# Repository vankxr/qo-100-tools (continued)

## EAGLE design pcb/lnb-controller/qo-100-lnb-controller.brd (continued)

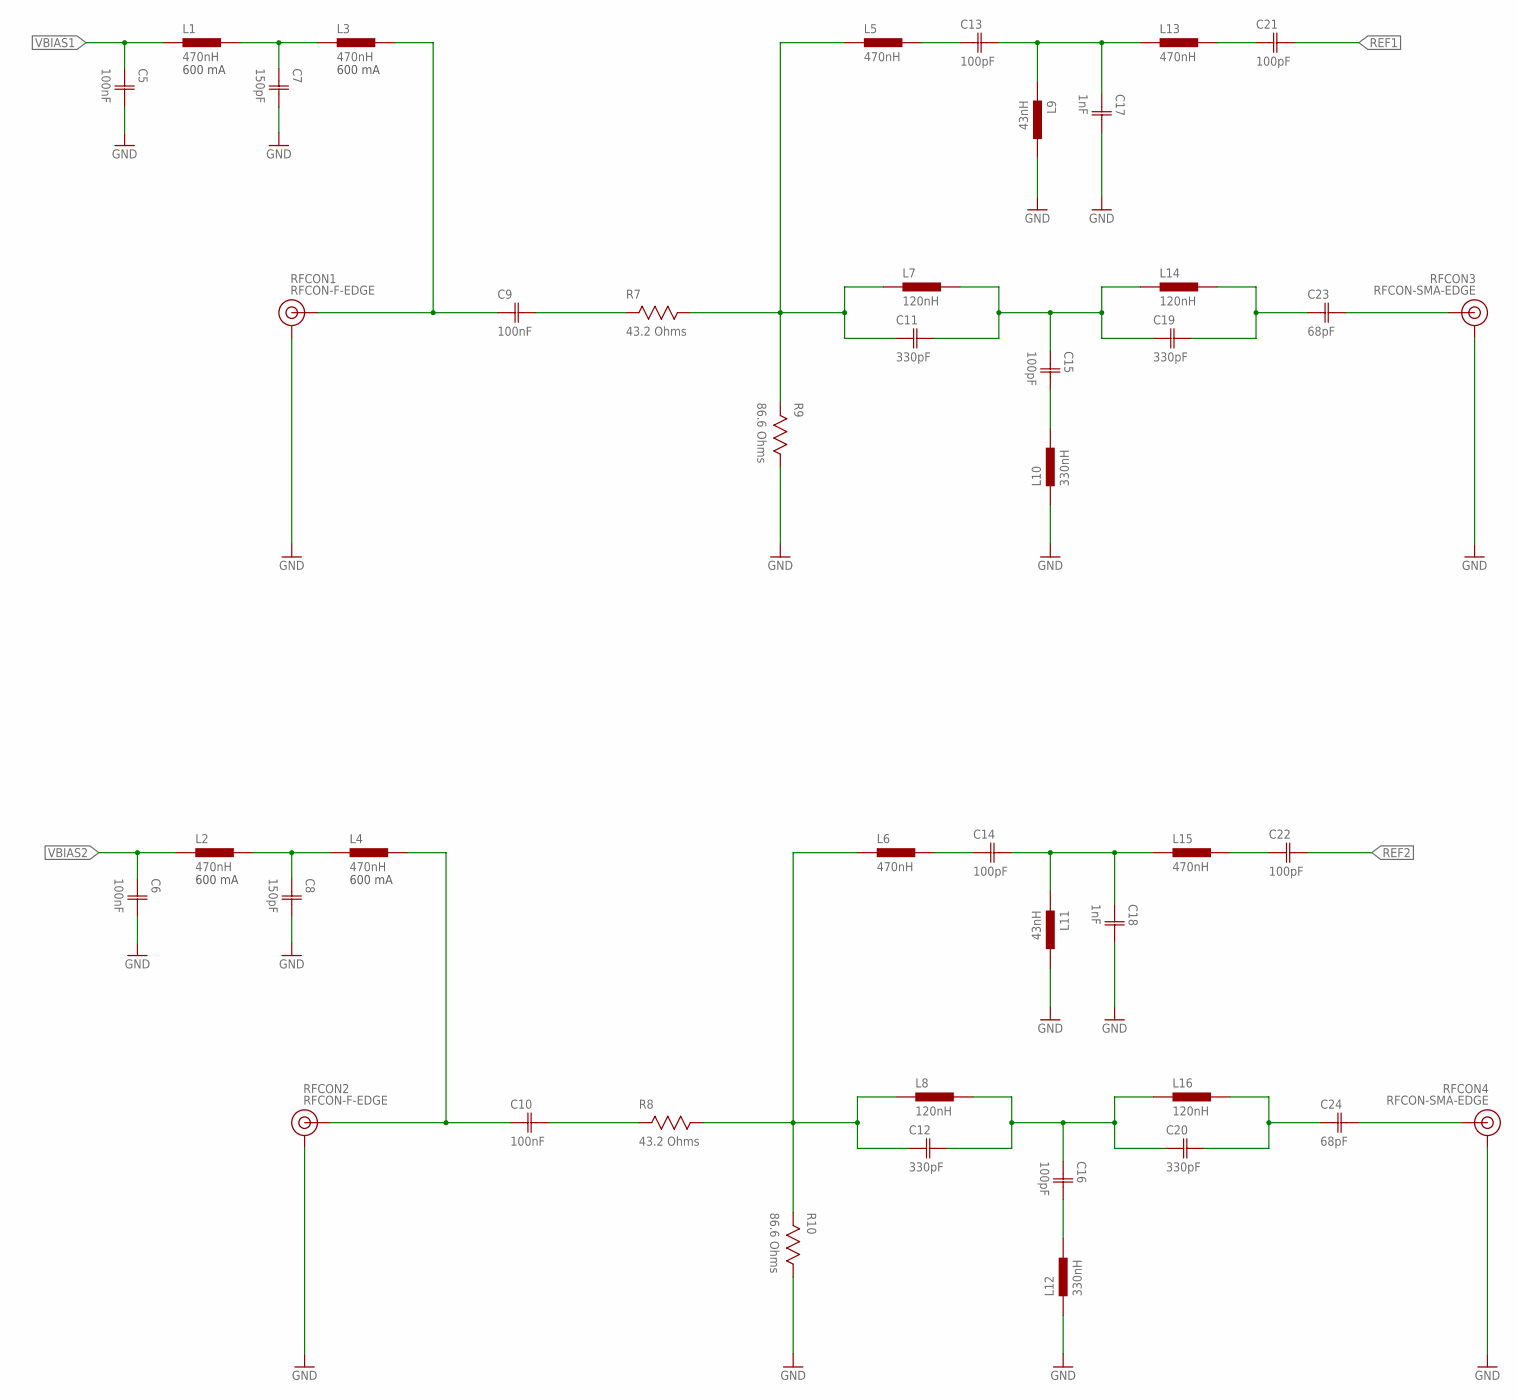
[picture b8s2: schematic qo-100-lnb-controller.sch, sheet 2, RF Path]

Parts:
C5, C6, C9, C10: 100nF; CAP0603
C7, C8: 150pF; CAP0603
C11, C12, C19, C20: 330pF; CAP0603
C13, C14, C15, C16, C21, C22: 100pF; CAP0603
C17, C18: 1nF; CAP0603
C23, C24: 68pF; CAP0603
L1, L2, L3, L4, L5, L6, L13, L15: 470nH; IND0603
L7, L8, L14, L16: 120nH; IND0603
L9, L11: 43nH; IND0603
L10, L12: 330nH; IND0603
R7, R8: 43.2 Ohms; RES0603
R9, R10: 86.6 Ohms; RES0603
RFCON1, RFCON2: RFCON-F-EDGE; F-EDGE
RFCON3, RFCON4: RFCON-SMA-EDGE; SMA-EDGE

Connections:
GND: C5.2 (C2), C6.2 (C2), C7.2 (C2), C8.2 (C2), C17.2 (C2), C18.2 (C2), L9.2, L10.1, L11.2, L12.1, R9.1, R10.1, RFCON1.GND@0 (GND), RFCON1.GND@1 (GND), RFCON1.GND@2 (GND), RFCON1.GND@3 (GND), RFCON1.GND@4 (GND), RFCON1.GND@5 (GND), RFCON2.GND@0 (GND), RFCON2.GND@1 (GND), RFCON2.GND@2 (GND), RFCON2.GND@3 (GND), RFCON2.GND@4 (GND), RFCON2.GND@5 (GND), RFCON3.GND@0 (GND), RFCON3.GND@1 (GND), RFCON3.GND@2 (GND), RFCON3.GND@3 (GND), RFCON4.GND@0 (GND), RFCON4.GND@1 (GND), RFCON4.GND@2 (GND), RFCON4.GND@3 (GND); also elsewhere on the board
unnamed: C9.1 (C1), L3.2, RFCON1.SIGNAL
unnamed: C9.2 (C2), R7.2
unnamed: C21.1 (C1), L13.2
unnamed: C7.1 (C1), L1.2, L3.1
unnamed: C13.1 (C1), L5.2
unnamed: C13.2 (C2), C17.1 (C1), L9.1, L13.1
unnamed: C19.2 (C2), C23.1 (C1), L14.2
unnamed: C11.1 (C1), L5.1, L7.1, R7.1, R9.2
unnamed: C11.2 (C2), C15.1 (C1), C19.1 (C1), L7.2, L14.1
unnamed: C23.2 (C2), RFCON3.SIG (SIGNAL)
unnamed: C15.2 (C2), L10.2
unnamed: C10.1 (C1), L4.2, RFCON2.SIGNAL
unnamed: C10.2 (C2), R8.2
unnamed: C8.1 (C1), L2.2, L4.1
unnamed: C22.1 (C1), L15.2
unnamed: C14.1 (C1), L6.2
unnamed: C14.2 (C2), C18.1 (C1), L11.1, L15.1
unnamed: C12.1 (C1), L6.1, L8.1, R8.1, R10.2
unnamed: C12.2 (C2), C16.1 (C1), C20.1 (C1), L8.2, L16.1
unnamed: C24.2 (C2), RFCON4.SIG (SIGNAL)
unnamed: C16.2 (C2), L12.2
unnamed: C20.2 (C2), C24.1 (C1), L16.2
REF1: C21.2 (C2); also elsewhere on the board
REF2: C22.2 (C2); also elsewhere on the board
VBIAS1: C5.1 (C1), L1.1; also elsewhere on the board
VBIAS2: C6.1 (C1), L2.1; also elsewhere on the board

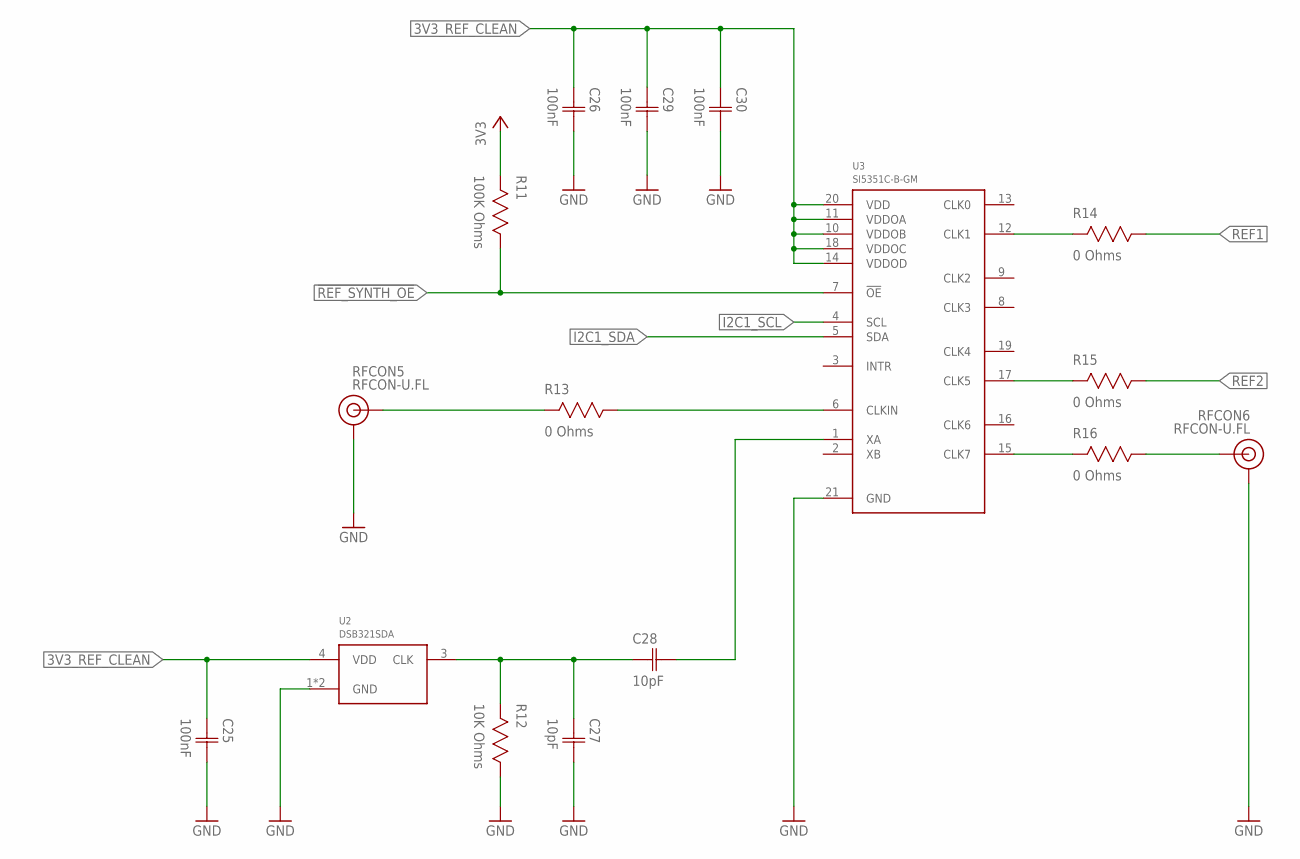
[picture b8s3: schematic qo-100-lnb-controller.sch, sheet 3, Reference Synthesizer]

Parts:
C25, C26, C29, C30: 100nF; CAP0603
C27, C28: 10pF; CAP0603
R11: 100K Ohms; RES0603
R12: 10K Ohms; RES0603
R13, R14, R15, R16: 0 Ohms; RES0603
RFCON5, RFCON6: RFCON-U.FL; U.FL
U2: DSB321SDA; TCXO-3225
U3: SI5351C-B-GM; QFN20

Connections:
3V3: R11.2; also elsewhere on the board
3V3_REF_CLEAN: C25.1 (C1), C26.1 (C1), C29.1 (C1), C30.1 (C1), U2.4 (VDD), U3.10 (VDDOB), U3.11 (VDDOA), U3.14 (VDDOD), U3.18 (VDDOC), U3.20 (VDD); also elsewhere on the board
!REF_SYNTH_OE: R11.1, U3.7 (!OE); also elsewhere on the board
EXT_REF_IN: R13.2, RFCON5.P$3 (SIGNAL)
EXT_REF_OUT: R16.1, RFCON6.P$3 (SIGNAL)
GND: C25.2 (C2), C26.2 (C2), C27.2 (C2), C29.2 (C2), C30.2 (C2), R12.1, RFCON5.P$1 (GND), RFCON5.P$2 (GND), RFCON6.P$1 (GND), RFCON6.P$2 (GND), U2.1 (GND), U2.2 (GND), U3.21 (GND); also elsewhere on the board
I2C1_SCL: U3.4 (SCL); also elsewhere on the board
I2C1_SDA: U3.5 (SDA); also elsewhere on the board
unnamed: R16.2, U3.15 (CLK7)
unnamed: R15.2, U3.17 (CLK5)
unnamed: R14.2, U3.12 (CLK1)
unnamed: C27.1 (C1), C28.1 (C1), R12.2, U2.3 (CLK)
unnamed: C28.2 (C2), U3.1 (XA)
unnamed: R13.1, U3.6 (CLKIN)
REF1: R14.1; also elsewhere on the board
REF2: R15.1; also elsewhere on the board

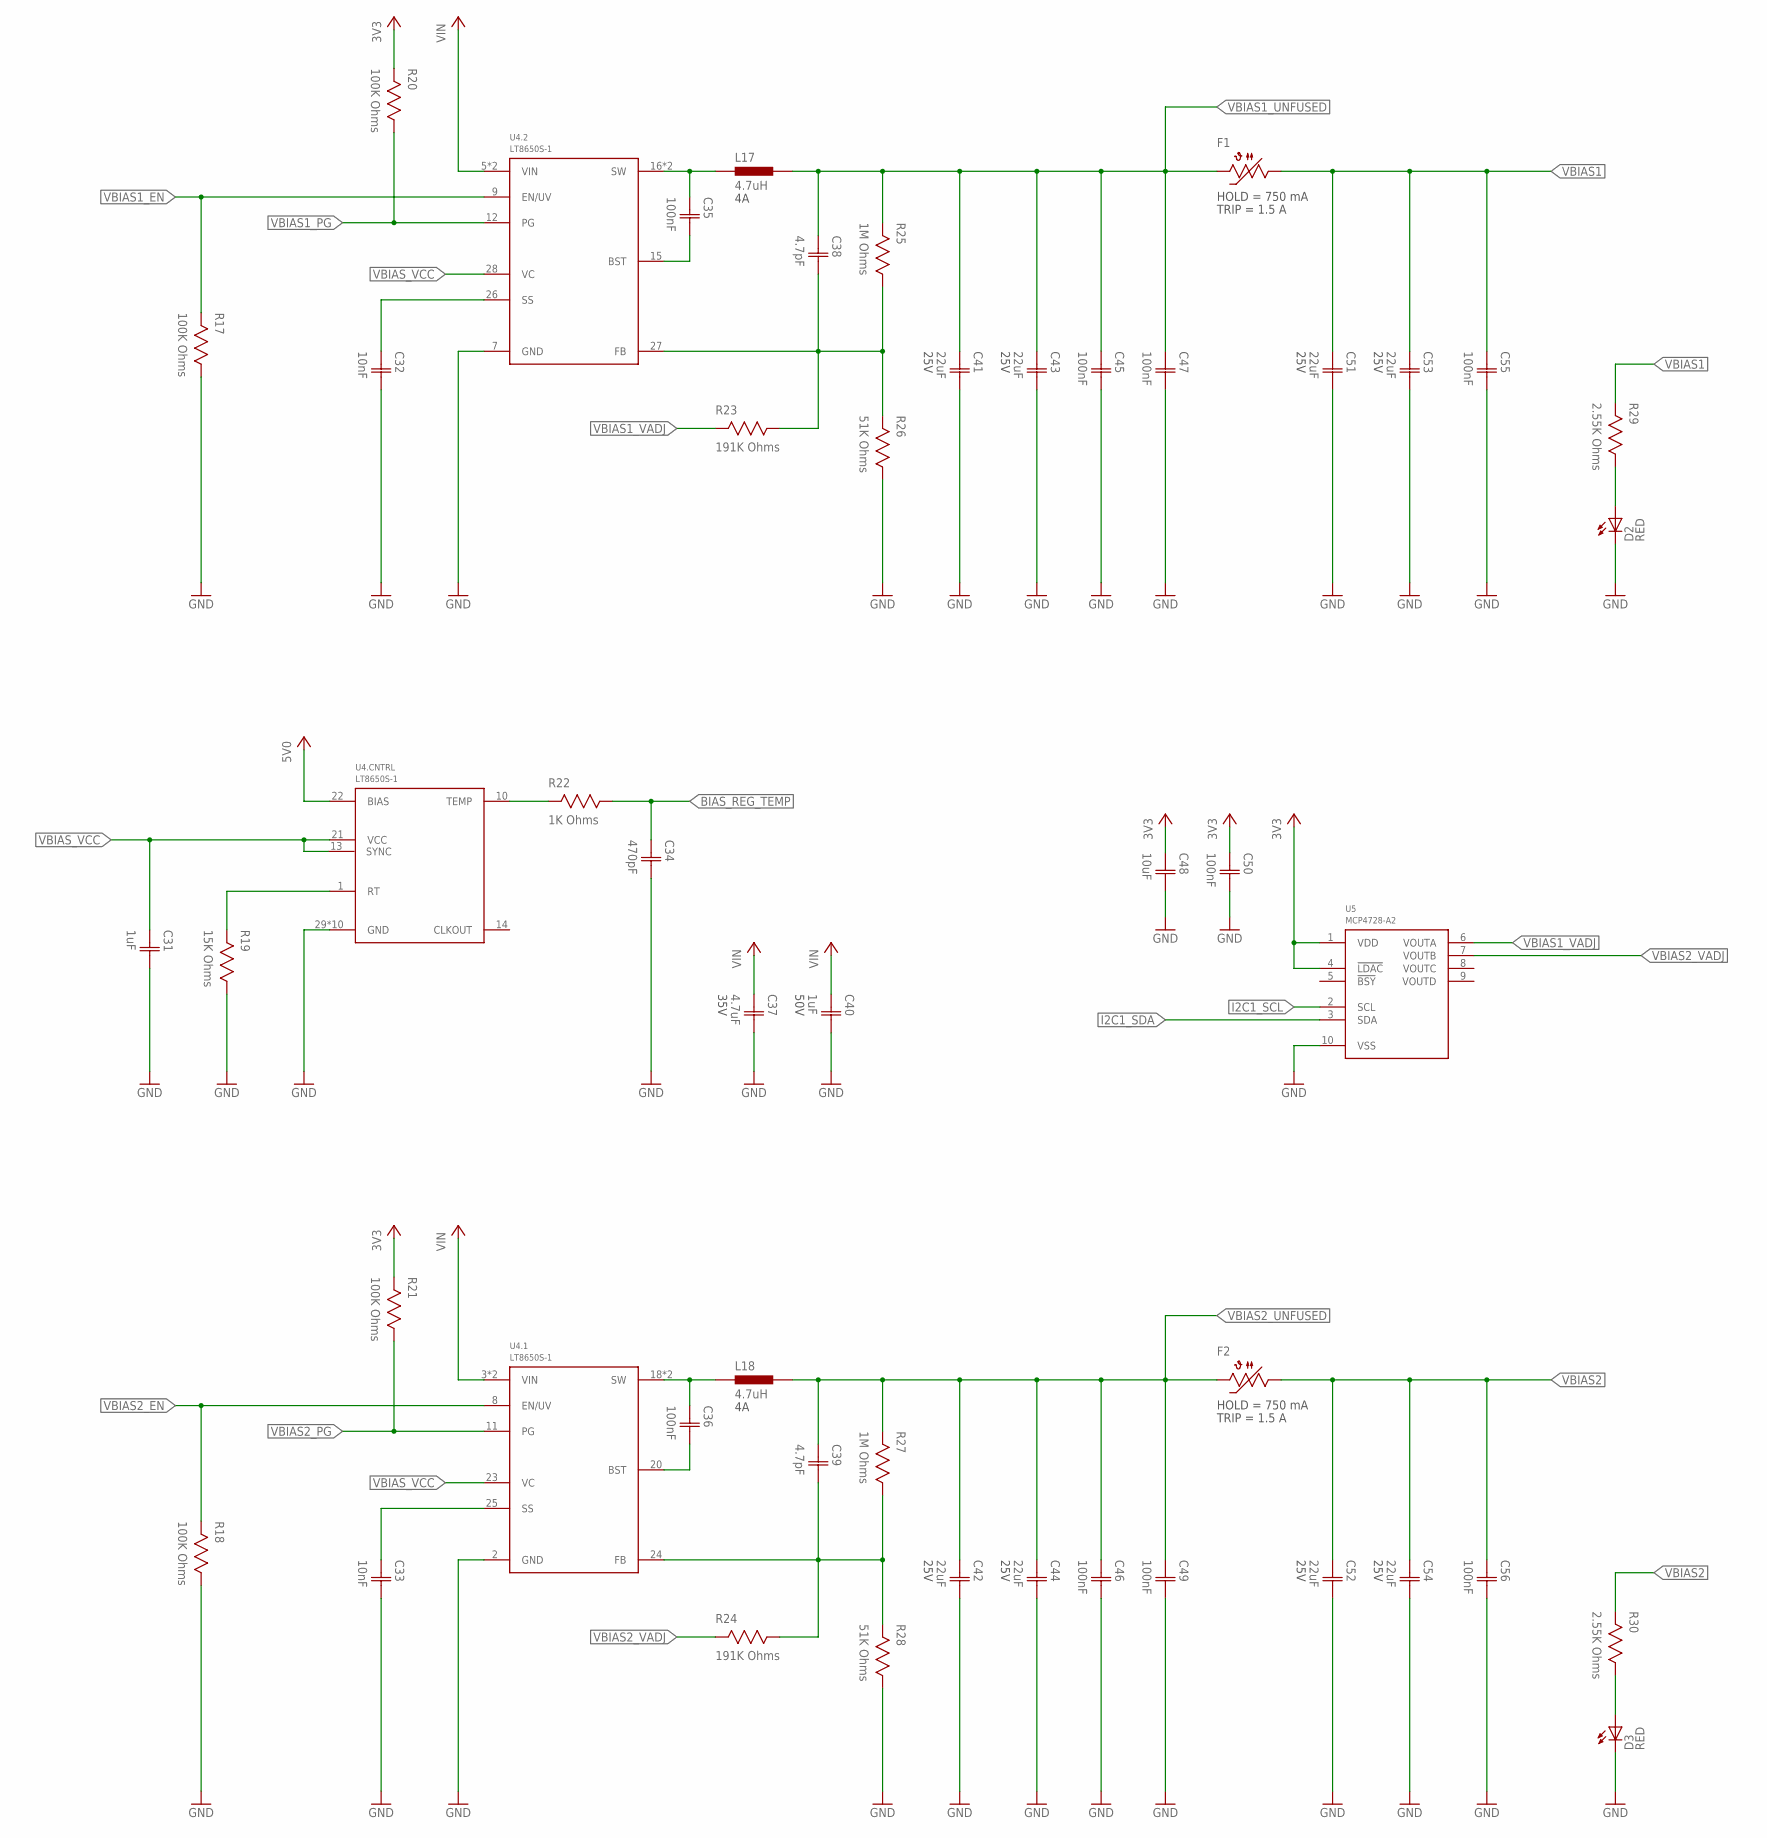
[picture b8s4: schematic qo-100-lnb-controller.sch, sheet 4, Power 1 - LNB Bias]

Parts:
C31: 1uF; CAP0603
C32, C33: 10nF; CAP0603
C34: 470pF; CAP0603
C35, C36, C45, C46, C47, C49, C50, C55, C56: 100nF; CAP0603
C37: 4.7uF; CAP0603; VOLTAGE 35V
C38, C39: 4.7pF; CAP0603
C40: 1uF; CAP0603; VOLTAGE 50V
C41, C42, C43, C44, C51, C52, C53, C54: 22uF; CAP1206; VOLTAGE 25V
C48: 10uF; CAP0603
D2, D3: LED0603; 0603
F1, F2: PTC0805; 0805
L17, L18: 4.7uH; IND0404
R17, R18, R20, R21: 100K Ohms; RES0603
R19: 15K Ohms; RES0603
R22: 1K Ohms; RES0603
R23, R24: 191K Ohms; RES0603
R25, R27: 1M Ohms; RES0603
R26, R28: 51K Ohms; RES0603
R29, R30: 2.55K Ohms; RES0603
U4: LT8650S-1; QFN28_ASYM_CORNER
U5: MCP4728-A2; MSOP10

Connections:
3V3: C48.1 (C1), C50.1 (C1), R20.2, R21.2, U5.1 (VDD), U5.4 (!LDAC); also elsewhere on the board
5V0: U4.22 (BIAS); also elsewhere on the board
BIAS_REG_TEMP: C34.1 (C1), R22.1; also elsewhere on the board
GND: C31.2 (C2), C32.2 (C2), C33.2 (C2), C34.2 (C2), C37.2 (C2), C40.2 (C2), C41.2 (C2), C42.2 (C2), C43.2 (C2), C44.2 (C2), C45.2 (C2), C46.2 (C2), C47.2 (C2), C48.2 (C2), C49.2 (C2), C50.2 (C2), C51.2 (C2), C52.2 (C2), C53.2 (C2), C54.2 (C2), C55.2 (C2), C56.2 (C2), D2.C, D3.C, R17.1, R18.1, R19.1, R26.1, R28.1, U4.2 (GND), U4.7 (GND), U4.29 (GND), U4.30 (GND), U4.31 (GND), U4.32 (GND), U4.33 (GND), U4.34 (GND), U4.35 (GND), U4.36 (GND), U4.37 (GND), U4.38 (GND), U5.10 (VSS); also elsewhere on the board
I2C1_SCL: U5.2 (SCL); also elsewhere on the board
I2C1_SDA: U5.3 (SDA); also elsewhere on the board
unnamed: R19.2, U4.1 (RT)
unnamed: R22.2, U4.10 (TEMP)
unnamed: D2.A, R29.1
unnamed: D3.A, R30.1
VBIAS1: C51.1 (C1), C53.1 (C1), C55.1 (C1), F1.1, R29.2; also elsewhere on the board
VBIAS1_BST: C35.2 (C2), U4.15 (BST)
VBIAS1_EN: R17.2, U4.9 (EN/UV); also elsewhere on the board
VBIAS1_FB: C38.2 (C2), R23.1, R25.1, R26.2, U4.27 (FB)
VBIAS1_PG: R20.1, U4.12 (PG); also elsewhere on the board
VBIAS1_SS: C32.1 (C1), U4.26 (SS)
VBIAS1_SW: C35.1 (C1), L17.1, U4.16 (SW), U4.17 (SW)
VBIAS1_UNFUSED: C38.1 (C1), C41.1 (C1), C43.1 (C1), C45.1 (C1), C47.1 (C1), F1.2, L17.2, R25.2
VBIAS1_VADJ: R23.2, U5.6 (VOUTA)
VBIAS2: C52.1 (C1), C54.1 (C1), C56.1 (C1), F2.1, R30.2; also elsewhere on the board
VBIAS2_BST: C36.2 (C2), U4.20 (BST)
VBIAS2_EN: R18.2, U4.8 (EN/UV); also elsewhere on the board
VBIAS2_FB: C39.2 (C2), R24.1, R27.1, R28.2, U4.24 (FB)
VBIAS2_PG: R21.1, U4.11 (PG); also elsewhere on the board
VBIAS2_SS: C33.1 (C1), U4.25 (SS)
VBIAS2_SW: C36.1 (C1), L18.1, U4.18 (SW), U4.19 (SW)
VBIAS2_UNFUSED: C39.1 (C1), C42.1 (C1), C44.1 (C1), C46.1 (C1), C49.1 (C1), F2.2, L18.2, R27.2
VBIAS2_VADJ: R24.2, U5.7 (VOUTB)
VBIAS_VCC: C31.1 (C1), U4.13 (SYNC), U4.21 (VCC), U4.23 (VC), U4.28 (VC)
VIN: C37.1 (C1), C40.1 (C1), U4.3 (VIN), U4.4 (VIN), U4.5 (VIN), U4.6 (VIN); also elsewhere on the board

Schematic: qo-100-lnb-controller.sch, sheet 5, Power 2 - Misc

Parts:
C57: 4.7uF; CAP0603; VOLTAGE 35V
C58: 4.7uF; CAP0603
C59, C60, C65, C69, C76: 470pF; CAP0603
C61, C62: 1uF; CAP0603; VOLTAGE 50V
C63, C73: 1uF; CAP0603
C64: 10nF; CAP0603
C66, C67, C72: 100nF; CAP0603
C68: 10pF; CAP0603
C70, C71: 100uF; CAP1206
C74: 10uF; CAP0603
C75: 10uF; CAP1206; VOLTAGE 50V
CON2: 2EDG-2P-5MM
D4: LED0603; 0603
D5: SMAJ24A; DO214AC
F3: 2.6A Hold; 1206
L19: 2.2uH; IND2520
L20: 4.7uH; IND2520
R31, R44: 100K Ohms; RES0603
R32: 10K Ohms; RES0603
R33, R38: 90.9K Ohms; RES0603
R34, R39: 12K Ohms; RES0603
R35: 41.2K Ohms; RES0603
R36: 309K Ohms; RES0603
R37: 71.5K Ohms; RES0603
R40: 1M Ohms; RES0603
R41: 226K Ohms; RES0603
R42: 510 Ohms; RES0603
R43: 75K Ohms; RES0603
U6: MIC23155; DFN10
U7: LT8636; QFN20_ASYM_CORNER
U8: ADP7142AUJZ-3.3; SOT23-5

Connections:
3V3: C66.1 (C1), C70.1 (C1), L19.2, R36.2, U6.3 (SNS); also elsewhere on the board
3V3_FB: R36.1, R37.2, U6.4 (FB)
3V3_REF_CLEAN: C74.1 (C1), U8.4 (SENSE/ADJ), U8.5 (VOUT); also elsewhere on the board
3V3_SOFTSTART: C60.1 (C1), U6.6 (SS)
3V3_SW: L19.1, U6.1 (SW)
5V0: C58.1 (C1), C68.1 (C1), C71.1 (C1), C72.1 (C1), C73.1 (C1), L20.2, R40.2, R42.2, R44.2, U6.2 (EN), U6.8 (VIN), U6.9 (VIN), U7.2 (BIAS), U8.1 (VIN), U8.3 (EN); also elsewhere on the board
5V0_BST: C67.2 (C2), U7.7 (BST)
5V0_FB: C68.2 (C2), R40.1, R41.2, U7.19 (FB), U7.20 (FB)
5V0_INTVCC: C63.1 (C1), U7.3 (INTVCC), U7.15 (SYNC/MODE)
5V0_RT: R35.2, U7.17 (RT)
5V0_SS: C64.1 (C1), U7.18 (TR/SS)
5V0_SW: C67.1 (C1), L20.1, U7.8 (SW), U7.9 (SW), U7.10 (SW)
5V0_VSENSE: C76.1 (C1), R43.2, R44.1; also elsewhere on the board
GND: C57.2 (C2), C58.2 (C2), C59.2 (C2), C60.2 (C2), C61.2 (C2), C62.2 (C2), C63.2 (C2), C64.2 (C2), C65.2 (C2), C66.2 (C2), C69.2 (C2), C70.2 (C2), C71.2 (C2), C72.2 (C2), C73.2 (C2), C74.2 (C2), C75.2 (C2), C76.2 (C2), CON2.P$1, D4.C, D5.A, R32.1, R34.1, R35.1, R37.1, R39.1, R41.1, R43.1, U6.7 (AGND), U6.10 (PGND), U6.11 (PGND), U7.4 (GND), U7.5 (GND), U7.12 (GND), U7.13 (GND), U7.21 (GND), U7.M1 (GND), U7.M2 (GND), U7.M3 (GND), U7.M4 (GND), U8.2 (GND); also elsewhere on the board
unnamed: CON2.P$2, F3.2
unnamed: D4.A, R42.1
VBIAS1: R33.2; also elsewhere on the board
VBIAS1_VSENSE: C65.1 (C1), R33.1, R34.2; also elsewhere on the board
VBIAS2: R38.2; also elsewhere on the board
VBIAS2_VSENSE: C69.1 (C1), R38.1, R39.2; also elsewhere on the board
VIN: C57.1 (C1), C61.1 (C1), C62.1 (C1), C75.1 (C1), D5.C, F3.1, R31.2, U7.6 (VIN), U7.11 (VIN), U7.14 (EN/UV); also elsewhere on the board
VIN_VSENSE: C59.1 (C1), R31.1, R32.2; also elsewhere on the board

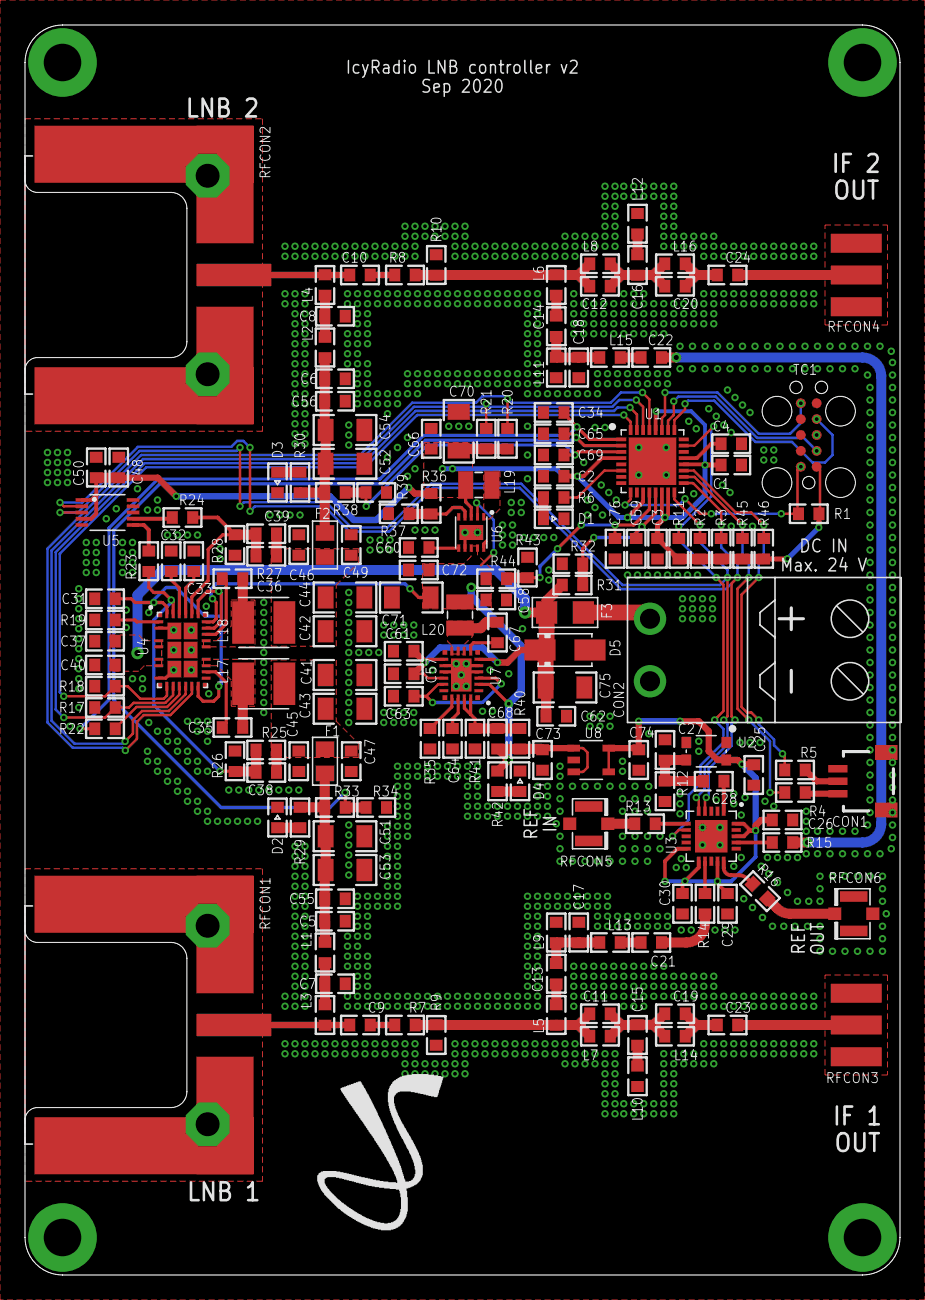
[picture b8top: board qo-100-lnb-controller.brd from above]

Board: 2 copper layers, 70.0 x 100.0 mm, 168 parts (0 on the bottom side), 90 nets.

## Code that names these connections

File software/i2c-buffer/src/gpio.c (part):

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    // Port A
    GPIO->P[0].CTRL   = GPIO_P_CTRL_DRIVESTRENGTHALT_STRONG | (5 << _GPIO_P_CTRL_SLEWRATEALT_SHIFT)
                      | GPIO_P_CTRL_DRIVESTRENGTH_STRONG | (5 << _GPIO_P_CTRL_SLEWRATE_SHIFT);
    GPIO->P[0].MODEL  = GPIO_P_MODEL_MODE0_PUSHPULL         // I2C_BUF_EN1
                      | GPIO_P_MODEL_MODE1_WIREDAND         // I2C_BIAS_EN2
                      | GPIO_P_MODEL_MODE2_DISABLED         // I2C_VBIAS2
                      | GPIO_P_MODEL_MODE3_DISABLED         // NC
                      | GPIO_P_MODEL_MODE4_DISABLED         // NC
                      | GPIO_P_MODEL_MODE5_DISABLED         // NC
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                      | GPIO_P_MODEL_MODE4_DISABLED         // NC
                      | GPIO_P_MODEL_MODE5_DISABLED         // NC
                      | GPIO_P_MODEL_MODE6_DISABLED         // NC
                      | GPIO_P_MODEL_MODE7_INPUT;           // I2C_SCL_BUF_SENSE2
    GPIO->P[1].MODEH  = GPIO_P_MODEH_MODE8_INPUT            // I2C_SCL_BUF_SENSE1
                      | GPIO_P_MODEH_MODE9_DISABLED         // NC
                      | GPIO_P_MODEH_MODE10_DISABLED        // NC
                      | GPIO_P_MODEH_MODE11_PUSHPULL        // I2C_BUF_EN2
                      | GPIO_P_MODEH_MODE12_DISABLED        // NC
                      | GPIO_P_MODEH_MODE13_WIREDAND        // I2C_BIAS_EN3
                      | GPIO_P_MODEH_MODE14_DISABLED        // I2C_VBIAS3
                      | GPIO_P_MODEH_MODE15_DISABLED;       // NC
    GPIO->P[1].DOUT   = 0;
    GPIO->P[1].OVTDIS = BIT(7) | BIT(8) | BIT(14);
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    // Port C
    GPIO->P[2].CTRL   = GPIO_P_CTRL_DRIVESTRENGTHALT_STRONG | (7 << _GPIO_P_CTRL_SLEWRATEALT_SHIFT)
                      | GPIO_P_CTRL_DRIVESTRENGTH_STRONG | (5 << _GPIO_P_CTRL_SLEWRATE_SHIFT);
    GPIO->P[2].MODEL  = GPIO_P_MODEL_MODE0_WIREDANDALTPULLUPFILTER // I2C0_SDA - Location 4
                      | GPIO_P_MODEL_MODE1_WIREDANDALTPULLUPFILTER // I2C0_SCL - Location 4
                      | GPIO_P_MODEL_MODE2_DISABLED                // NC
                      | GPIO_P_MODEL_MODE3_DISABLED                // NC
                      | GPIO_P_MODEL_MODE4_DISABLED                // NC
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                      | GPIO_P_MODEH_MODE10_DISABLED               // NC
                      | GPIO_P_MODEH_MODE11_DISABLED               // NC
                      | GPIO_P_MODEH_MODE12_DISABLED               // NC
                      | GPIO_P_MODEH_MODE13_PUSHPULL               // I2C_BUF_EN4
                      | GPIO_P_MODEH_MODE14_INPUT                  // I2C_SCL_BUF_SENSE4
                      | GPIO_P_MODEH_MODE15_INPUT;                 // I2C_SCL_BUF_SENSE3
    GPIO->P[2].DOUT   = 0;
    GPIO->P[2].OVTDIS = BIT(14) | BIT(15);

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                      | GPIO_P_MODEL_MODE1_DISABLED                 // NC
                      | GPIO_P_MODEL_MODE2_DISABLED                 // NC
                      | GPIO_P_MODEL_MODE3_DISABLED                 // NC
                      | GPIO_P_MODEL_MODE4_PUSHPULL                 // I2C_BUF_EN3
                      | GPIO_P_MODEL_MODE5_WIREDAND                 // I2C_BIAS_EN4
                      | GPIO_P_MODEL_MODE6_DISABLED                 // I2C_VBIAS4
                      | GPIO_P_MODEL_MODE7_DISABLED;                // NU
    GPIO->P[3].MODEH  = GPIO_P_MODEH_MODE8_DISABLED                 // NC
                      | GPIO_P_MODEH_MODE9_DISABLED                 // NC
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                      | GPIO_P_MODEH_MODE9_DISABLED                 // NC
                      | GPIO_P_MODEH_MODE10_PUSHPULL                // LED
                      | GPIO_P_MODEH_MODE11_DISABLED                // NU
                      | GPIO_P_MODEH_MODE12_WIREDAND                // I2C_BIAS_EN1
                      | GPIO_P_MODEH_MODE13_DISABLED                // I2C_VBIAS1
                      | GPIO_P_MODEH_MODE14_DISABLED                // NC
                      | GPIO_P_MODEH_MODE15_DISABLED;               // NC
    GPIO->P[4].DOUT   = 0;
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
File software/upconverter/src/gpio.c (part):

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    GPIO->P[0].CTRL   = GPIO_P_CTRL_DRIVESTRENGTHALT_STRONG | (5 << _GPIO_P_CTRL_SLEWRATEALT_SHIFT)
                      | GPIO_P_CTRL_DRIVESTRENGTH_STRONG | (5 << _GPIO_P_CTRL_SLEWRATE_SHIFT);
    GPIO->P[0].MODEL  = GPIO_P_MODEL_MODE0_DISABLED     // VPDET_VSENSE
                      | GPIO_P_MODEL_MODE1_PUSHPULL     // RF_ATT1_LE
                      | GPIO_P_MODEL_MODE2_PUSHPULL     // RF_ATT2_LE
                      | GPIO_P_MODEL_MODE3_DISABLED     // NC
                      | GPIO_P_MODEL_MODE4_DISABLED     // NC
                      | GPIO_P_MODEL_MODE5_DISABLED     // NC
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                      | GPIO_P_MODEL_MODE4_DISABLED         // NC
                      | GPIO_P_MODEL_MODE5_DISABLED         // NC
                      | GPIO_P_MODEL_MODE6_DISABLED         // NC
                      | GPIO_P_MODEL_MODE7_PUSHPULL;        // PA_STG1_2_BIAS_EN
    GPIO->P[1].MODEH  = GPIO_P_MODEH_MODE8_PUSHPULL         // PA_STG3_BIAS_EN
                      | GPIO_P_MODEH_MODE9_DISABLED         // NC
                      | GPIO_P_MODEH_MODE10_DISABLED        // NC
                      | GPIO_P_MODEH_MODE11_PUSHPULL        // LED
                      | GPIO_P_MODEH_MODE12_DISABLED        // NC
                      | GPIO_P_MODEH_MODE13_DISABLED        // 5V0_VSENSE
                      | GPIO_P_MODEH_MODE14_DISABLED        // VIN_VSENSE
                      | GPIO_P_MODEH_MODE15_DISABLED;       // NC
    GPIO->P[1].DOUT   = 0;
    GPIO->P[1].OVTDIS = BIT(13) | BIT(14);
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    // Port C
    GPIO->P[2].CTRL   = GPIO_P_CTRL_DRIVESTRENGTHALT_STRONG | (5 << _GPIO_P_CTRL_SLEWRATEALT_SHIFT)
                      | GPIO_P_CTRL_DRIVESTRENGTH_STRONG | (5 << _GPIO_P_CTRL_SLEWRATE_SHIFT);
    GPIO->P[2].MODEL  = GPIO_P_MODEL_MODE0_WIREDANDPULLUPFILTER     // I2C0_SDA - Location 4
                      | GPIO_P_MODEL_MODE1_WIREDANDPULLUPFILTER     // I2C0_SCL - Location 4
                      | GPIO_P_MODEL_MODE2_DISABLED                 // NC
                      | GPIO_P_MODEL_MODE3_DISABLED                 // NC
                      | GPIO_P_MODEL_MODE4_DISABLED                 // NC
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                      | GPIO_P_MODEH_MODE11_DISABLED                // NC
                      | GPIO_P_MODEH_MODE12_DISABLED                // NC
                      | GPIO_P_MODEH_MODE13_DISABLED                // NU
                      | GPIO_P_MODEH_MODE14_PUSHPULL                // PLL_EN
                      | GPIO_P_MODEH_MODE15_PUSHPULL;               // PLL_LE
    GPIO->P[2].DOUT   = BIT(15);
    GPIO->P[2].OVTDIS = 0;

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                      | GPIO_P_MODEL_MODE1_DISABLED                 // NC
                      | GPIO_P_MODEL_MODE2_DISABLED                 // NC
                      | GPIO_P_MODEL_MODE3_DISABLED                 // NC
                      | GPIO_P_MODEL_MODE4_WIREDANDPULLUPFILTER     // I2C1_SDA - Location 3
                      | GPIO_P_MODEL_MODE5_WIREDANDPULLUPFILTER     // I2C1_SCL - Location 3
                      | GPIO_P_MODEL_MODE6_PUSHPULL                 // IF_ATT_LE
                      | GPIO_P_MODEL_MODE7_PUSHPULL;                // nMIXER_SHDN
    GPIO->P[3].MODEH  = GPIO_P_MODEH_MODE8_DISABLED                 // NC
                      | GPIO_P_MODEH_MODE9_DISABLED                 // NC
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                      | GPIO_P_MODEL_MODE7_DISABLED;                // NC
    GPIO->P[4].MODEH  = GPIO_P_MODEH_MODE8_DISABLED                 // NC
                      | GPIO_P_MODEH_MODE9_DISABLED                 // NC
                      | GPIO_P_MODEH_MODE10_PUSHPULL                // SPI_MOSI (USART0_TX - Location 0)
                      | GPIO_P_MODEH_MODE11_INPUTPULLFILTER         // PLL_MUXOUT
                      | GPIO_P_MODEH_MODE12_PUSHPULL                // SPI_SCK (USART0_CLK - Location 0)
                      | GPIO_P_MODEH_MODE13_PUSHPULL                // nPLL_MUTE
                      | GPIO_P_MODEH_MODE14_DISABLED                // NC
                      | GPIO_P_MODEH_MODE15_DISABLED;               // NC
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
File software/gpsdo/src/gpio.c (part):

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    // Port A
    GPIO->P[0].CTRL   = GPIO_P_CTRL_DRIVESTRENGTHALT_STRONG | (5 << _GPIO_P_CTRL_SLEWRATEALT_SHIFT)
                      | GPIO_P_CTRL_DRIVESTRENGTH_STRONG | (5 << _GPIO_P_CTRL_SLEWRATE_SHIFT);
    GPIO->P[0].MODEL  = GPIO_P_MODEL_MODE0_PUSHPULL                 // GPS_RXD - USART3 - Location 0
                      | GPIO_P_MODEL_MODE1_INPUTPULL                // GPS_TXD - USART3 - Location 0 / GPS_TXREADY
                      | GPIO_P_MODEL_MODE2_PUSHPULL                 // nGPS_RESET
                      | GPIO_P_MODEL_MODE3_DISABLED                 // NR
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    GPIO->P[1].MODEH  = GPIO_P_MODEH_MODE8_DISABLED                 // NR
                      | GPIO_P_MODEH_MODE9_DISABLED                 // NR
                      | GPIO_P_MODEH_MODE10_DISABLED                // NR
                      | GPIO_P_MODEH_MODE11_WIREDANDALTPULLUPFILTER // I2C1_SDA - I2C1 - Location 1
                      | GPIO_P_MODEH_MODE12_WIREDANDALTPULLUPFILTER // I2C1_SCL - I2C1 - Location 1
                      | GPIO_P_MODEH_MODE13_PUSHPULL                // MCU_LED
                      | GPIO_P_MODEH_MODE14_DISABLED                // NR
                      | GPIO_P_MODEH_MODE15_DISABLED;               // NR
    GPIO->P[1].DOUT   = 0;
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                      | GPIO_P_MODEL_MODE1_DISABLED                 // NR
                      | GPIO_P_MODEL_MODE2_DISABLED                 // NR
                      | GPIO_P_MODEL_MODE3_DISABLED                 // NR
                      | GPIO_P_MODEL_MODE4_DISABLED                 // VIN_VSENSE
                      | GPIO_P_MODEL_MODE5_DISABLED                 // NR
                      | GPIO_P_MODEL_MODE6_DISABLED                 // 5V0_VSENSE
                      | GPIO_P_MODEL_MODE7_DISABLED;                // NR
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                      | GPIO_P_MODEL_MODE5_DISABLED                 // NR
                      | GPIO_P_MODEL_MODE6_DISABLED                 // NR
                      | GPIO_P_MODEL_MODE7_DISABLED;                // NR
    GPIO->P[4].MODEH  = GPIO_P_MODEH_MODE8_WIREDANDALTPULLUPFILTER  // I2C2_SDA - I2C2 - Location 0
                      | GPIO_P_MODEH_MODE9_DISABLED                 // NR
                      | GPIO_P_MODEH_MODE10_PUSHPULL                // DAC_DIN - USART0 - Location 0
                      | GPIO_P_MODEH_MODE11_PUSHPULL                // OCXO_EN
                      | GPIO_P_MODEH_MODE12_PUSHPULL                // DAC_SCLK - USART0 - Location 0
                      | GPIO_P_MODEH_MODE13_PUSHPULL                // nDAC_CS - USART0 - Location 0
                      | GPIO_P_MODEH_MODE14_DISABLED                // NR
                      | GPIO_P_MODEH_MODE15_INPUTPULL;              // GPS_TIMEPULSE_BUF
    GPIO->P[4].DOUT   = BIT(13);
    GPIO->P[4].OVTDIS = 0;

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                      | GPIO_P_MODEL_MODE2_PUSHPULL                 // DBG_SWO - Location 0
                      | GPIO_P_MODEL_MODE3_DISABLED                 // NC
                      | GPIO_P_MODEL_MODE4_DISABLED                 // NC
                      | GPIO_P_MODEL_MODE5_WIREDANDALTPULLUPFILTER  // I2C2_SCL - I2C2 - Location 0
                      | GPIO_P_MODEL_MODE6_DISABLED                 // NR
                      | GPIO_P_MODEL_MODE7_PUSHPULL;                // nPLL_RESET
    GPIO->P[5].MODEH  = GPIO_P_MODEH_MODE8_DISABLED                 // NR
                      | GPIO_P_MODEH_MODE9_DISABLED                 // NR
                      | GPIO_P_MODEH_MODE10_DISABLED                // NR
                      | GPIO_P_MODEH_MODE11_DISABLED                // NR
                      | GPIO_P_MODEH_MODE12_INPUTPULL               // OCXO_CLK_BUF
                      | GPIO_P_MODEH_MODE13_DISABLED                // NC
                      | GPIO_P_MODEH_MODE14_DISABLED                // NC
                      | GPIO_P_MODEH_MODE15_DISABLED;               // NC
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
    // Debugger Route
    GPIO->ROUTEPEN &= ~(GPIO_ROUTEPEN_TDIPEN | GPIO_ROUTEPEN_TDOPEN);   // Disable JTAG
    GPIO->ROUTEPEN |= GPIO_ROUTEPEN_SWVPEN;                             // Enable SWO
    GPIO->ROUTELOC0 = GPIO_ROUTELOC0_SWVLOC_LOC0;                       // SWO on PF2

    // External interrupts
    GPIO->EXTIPSELL = GPIO_EXTIPSELL_EXTIPSEL0_PORTA            // NU
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                    | GPIO_EXTIPSELH_EXTIPSEL9_PORTA            // NU
                    | GPIO_EXTIPSELH_EXTIPSEL10_PORTA           // NU
                    | GPIO_EXTIPSELH_EXTIPSEL11_PORTA           // NU
                    | GPIO_EXTIPSELH_EXTIPSEL12_PORTF           // OCXO_CLK_BUF
                    | GPIO_EXTIPSELH_EXTIPSEL13_PORTE           // GPS_TIMEPULSE_BUF
                    | GPIO_EXTIPSELH_EXTIPSEL14_PORTA           // NU
                    | GPIO_EXTIPSELH_EXTIPSEL15_PORTA;          // NU

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                      | GPIO_EXTIPINSELH_EXTIPINSEL9_PIN8       // NU
                      | GPIO_EXTIPINSELH_EXTIPINSEL10_PIN8      // NU
                      | GPIO_EXTIPINSELH_EXTIPINSEL11_PIN8      // NU
                      | GPIO_EXTIPINSELH_EXTIPINSEL12_PIN12     // OCXO_CLK_BUF
                      | GPIO_EXTIPINSELH_EXTIPINSEL13_PIN15     // GPS_TIMEPULSE_BUF
                      | GPIO_EXTIPINSELH_EXTIPINSEL14_PIN12     // NU
                      | GPIO_EXTIPINSELH_EXTIPINSEL15_PIN12;    // NU

    GPIO->EXTIRISE = BIT(13); // GPS_TIMEPULSE_BUF
    GPIO->EXTIFALL = BIT(8) | BIT(13); // nPLL_IRQ, GPS_TIMEPULSE_BUF

    GPIO->IFC = _GPIO_IFC_MASK; // Clear pending IRQs
    IRQ_CLEAR(GPIO_EVEN_IRQn); // Clear pending vector
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
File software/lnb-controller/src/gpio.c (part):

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    // Port A
    GPIO->P[0].CTRL   = GPIO_P_CTRL_DRIVESTRENGTHALT_STRONG | (5 << _GPIO_P_CTRL_SLEWRATEALT_SHIFT)
                      | GPIO_P_CTRL_DRIVESTRENGTH_STRONG | (5 << _GPIO_P_CTRL_SLEWRATE_SHIFT);
    GPIO->P[0].MODEL  = GPIO_P_MODEL_MODE0_DISABLED     // BIAS_REG_TEMP
                      | GPIO_P_MODEL_MODE1_DISABLED     // VBIAS1_VSENSE
                      | GPIO_P_MODEL_MODE2_DISABLED     // VBIAS2_VSENSE
                      | GPIO_P_MODEL_MODE3_DISABLED     // NC
                      | GPIO_P_MODEL_MODE4_DISABLED     // NC
                      | GPIO_P_MODEL_MODE5_DISABLED     // NC
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                      | GPIO_P_MODEH_MODE11_DISABLED        // NU
                      | GPIO_P_MODEH_MODE12_DISABLED        // NC
                      | GPIO_P_MODEH_MODE13_DISABLED        // 5V0_VSENSE
                      | GPIO_P_MODEH_MODE14_DISABLED        // VIN_VSENSE
                      | GPIO_P_MODEH_MODE15_DISABLED;       // NC
    GPIO->P[1].DOUT   = 0;
    GPIO->P[1].OVTDIS = BIT(13) | BIT(14);
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                      | GPIO_P_MODEL_MODE1_DISABLED                 // NC
                      | GPIO_P_MODEL_MODE2_DISABLED                 // NC
                      | GPIO_P_MODEL_MODE3_DISABLED                 // NC
                      | GPIO_P_MODEL_MODE4_WIREDANDPULLUPFILTER     // I2C1_SDA - Location 3
                      | GPIO_P_MODEL_MODE5_WIREDANDPULLUPFILTER     // I2C1_SCL - Location 3
                      | GPIO_P_MODEL_MODE6_WIREDANDALTPULLUPFILTER  // I2C0_SDA - Location 1
                      | GPIO_P_MODEL_MODE7_WIREDANDALTPULLUPFILTER; // I2C0_SCL - Location 1
    GPIO->P[3].MODEH  = GPIO_P_MODEH_MODE8_DISABLED                 // NC
                      | GPIO_P_MODEH_MODE9_DISABLED                 // NC
                      | GPIO_P_MODEH_MODE10_DISABLED                // NC
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                      | GPIO_P_MODEL_MODE7_DISABLED;                // NC
    GPIO->P[4].MODEH  = GPIO_P_MODEH_MODE8_DISABLED                 // NC
                      | GPIO_P_MODEH_MODE9_DISABLED                 // NC
                      | GPIO_P_MODEH_MODE10_INPUTPULLFILTER         // VBIAS1_PG
                      | GPIO_P_MODEH_MODE11_INPUTPULLFILTER         // VBIAS2_PG
                      | GPIO_P_MODEH_MODE12_PUSHPULL                // VBIAS1_EN
                      | GPIO_P_MODEH_MODE13_PUSHPULL                // VBIAS2_EN
                      | GPIO_P_MODEH_MODE14_DISABLED                // NC
                      | GPIO_P_MODEH_MODE15_DISABLED;               // NC
    GPIO->P[4].DOUT   = BIT(10) | BIT(11);
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
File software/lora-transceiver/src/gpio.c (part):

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    // Port A
    GPIO->P[0].CTRL   = GPIO_P_CTRL_DRIVESTRENGTHALT_STRONG | (5 << _GPIO_P_CTRL_SLEWRATEALT_SHIFT)
                      | GPIO_P_CTRL_DRIVESTRENGTH_STRONG | (5 << _GPIO_P_CTRL_SLEWRATE_SHIFT);
    GPIO->P[0].MODEL  = GPIO_P_MODEL_MODE0_INPUTPULLFILTER  // LORA_DIO5
                      | GPIO_P_MODEL_MODE1_INPUTPULLFILTER  // LORA_DIO4
                      | GPIO_P_MODEL_MODE2_INPUTPULLFILTER  // LORA_DIO3
                      | GPIO_P_MODEL_MODE3_DISABLED         // NC
                      | GPIO_P_MODEL_MODE4_DISABLED         // NC
                      | GPIO_P_MODEL_MODE5_DISABLED         // NC
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                      | GPIO_P_MODEL_MODE4_DISABLED         // NC
                      | GPIO_P_MODEL_MODE5_DISABLED         // NC
                      | GPIO_P_MODEL_MODE6_DISABLED         // NC
                      | GPIO_P_MODEL_MODE7_INPUTPULLFILTER; // LORA_DIO0
    GPIO->P[1].MODEH  = GPIO_P_MODEH_MODE8_PUSHPULL         // LED
                      | GPIO_P_MODEH_MODE9_DISABLED         // NC
                      | GPIO_P_MODEH_MODE10_DISABLED        // NC
                      | GPIO_P_MODEH_MODE11_PUSHPULL        // nLORA_RESET
                      | GPIO_P_MODEH_MODE12_DISABLED        // NC
                      | GPIO_P_MODEH_MODE13_DISABLED        // 5V0_VSENSE
                      | GPIO_P_MODEH_MODE14_DISABLED        // VIN_VSENSE
                      | GPIO_P_MODEH_MODE15_DISABLED;       // NC
    GPIO->P[1].DOUT   = 0;
    GPIO->P[1].OVTDIS = BIT(13) | BIT(14);
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    // Port C
    GPIO->P[2].CTRL   = GPIO_P_CTRL_DRIVESTRENGTHALT_STRONG | (5 << _GPIO_P_CTRL_SLEWRATEALT_SHIFT)
                      | GPIO_P_CTRL_DRIVESTRENGTH_STRONG | (5 << _GPIO_P_CTRL_SLEWRATE_SHIFT);
    GPIO->P[2].MODEL  = GPIO_P_MODEL_MODE0_INPUTPULLFILTER      // LORA_DIO2
                      | GPIO_P_MODEL_MODE1_INPUTPULLFILTER      // LORA_DIO1
                      | GPIO_P_MODEL_MODE2_DISABLED             // NC
                      | GPIO_P_MODEL_MODE3_DISABLED             // NC
                      | GPIO_P_MODEL_MODE4_DISABLED             // NC
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                      | GPIO_P_MODEL_MODE3_DISABLED                 // NC
                      | GPIO_P_MODEL_MODE4_DISABLED                 // NU
                      | GPIO_P_MODEL_MODE5_DISABLED                 // NU
                      | GPIO_P_MODEL_MODE6_WIREDANDPULLUPFILTER     // I2C0_SDA - Location 1
                      | GPIO_P_MODEL_MODE7_WIREDANDPULLUPFILTER;    // I2C0_SCL - Location 1
    GPIO->P[3].MODEH  = GPIO_P_MODEH_MODE8_DISABLED                 // NC
                      | GPIO_P_MODEH_MODE9_DISABLED                 // NC
                      | GPIO_P_MODEH_MODE10_DISABLED                // NC
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                      | GPIO_P_MODEL_MODE7_DISABLED;                // NC
    GPIO->P[4].MODEH  = GPIO_P_MODEH_MODE8_DISABLED                 // NC
                      | GPIO_P_MODEH_MODE9_DISABLED                 // NC
                      | GPIO_P_MODEH_MODE10_PUSHPULL                // SPI_MOSI (USART0_TX - Location 0)
                      | GPIO_P_MODEH_MODE11_INPUTPULL               // SPI_MISO (USART0_RX - Location 0)
                      | GPIO_P_MODEH_MODE12_PUSHPULL                // SPI_SCK (USART0_CLK - Location 0)
                      | GPIO_P_MODEH_MODE13_PUSHPULL                // nLORA_CS (USART0_CS - Location 0)
                      | GPIO_P_MODEH_MODE14_DISABLED                // NC
                      | GPIO_P_MODEH_MODE15_DISABLED;               // NC
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
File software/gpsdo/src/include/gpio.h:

#ifndef __GPIO_H__
#define __GPIO_H__

#include <em_device.h>
#include "cmu.h"
#include "systick.h"
#include "utils.h"
#include "nvic.h"

// LED MACROS
#define LED_HIGH()              PERI_REG_BIT_SET(&(GPIO->P[1].DOUT)) = BIT(13)
#define LED_LOW()               PERI_REG_BIT_CLEAR(&(GPIO->P[1].DOUT)) = BIT(13)
#define LED_TOGGLE()            GPIO->P[1].DOUTTGL = BIT(13);
#define LED_STATUS()            !!(GPIO->P[1].DOUT & BIT(13))

// POWER MACROS
#define PWR_3V3_PGOOD()         PERI_REG_BIT(&(GPIO->P[0].DIN), 6)
#define PWR_1V8_PLL_ENABLE()    PERI_REG_BIT_SET(&(GPIO->P[0].DOUT)) = BIT(6)
#define PWR_1V8_PLL_DISABLE()   PERI_REG_BIT_CLEAR(&(GPIO->P[0].DOUT)) = BIT(6)
#define PWR_OCXO_ENABLE()       PERI_REG_BIT_SET(&(GPIO->P[4].DOUT)) = BIT(11)
#define PWR_OCXO_DISABLE()      PERI_REG_BIT_CLEAR(&(GPIO->P[4].DOUT)) = BIT(11)
#define PWR_OCXO_STATUS()       PERI_REG_BIT(&(GPIO->P[4].DIN), 11)

// DAC MACROS
#define DAC_SELECT()            PERI_REG_BIT_CLEAR(&(GPIO->P[4].DOUT)) = BIT(13)
#define DAC_UNSELECT()          PERI_REG_BIT_SET(&(GPIO->P[4].DOUT)) = BIT(13)

// PLL MACROS
#define PLL_RESET()             PERI_REG_BIT_CLEAR(&(GPIO->P[5].DOUT)) = BIT(7)
#define PLL_UNRESET()           PERI_REG_BIT_SET(&(GPIO->P[5].DOUT)) = BIT(7)

// GPS MACROS
#define GPS_TIMEPULSE()         PERI_REG_BIT(&(GPIO->P[4].DIN), 15)
#define GPS_TX_READY()          PERI_REG_BIT(&(GPIO->P[0].DIN), 1)
#define GPS_RESET()             PERI_REG_BIT_CLEAR(&(GPIO->P[0].DOUT)) = BIT(2)
#define GPS_UNRESET()           PERI_REG_BIT_SET(&(GPIO->P[0].DOUT)) = BIT(2)

void gpio_init();

#endif  // __GPIO_H__
